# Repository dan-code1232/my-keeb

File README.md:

# my-keeb
My keeb design and documents for the hack club keeb YSWS
TOTAL OF 32 hours learning and building

This YSWS was my first hack club project. I learnt about hackclub from online and I had a great time building and completeing this project. During theis project I made a custom keyboard with programmable macro keys and learnt 3d onshape design, soldering,kicad pcb design and also about different styles layouts and mounts of keyboards.My finished project was one that i am proud of and here it is!

##AND THE FINAL RENDER::

https://cad.onshape.com/documents/12cb8831dddddaf00ecb411f/w/8d695212fe769afe4ca3f804/e/d073d4997be6d06dd7fe0af7?renderMode=0&uiState=6adc6b124070a14a067048c0

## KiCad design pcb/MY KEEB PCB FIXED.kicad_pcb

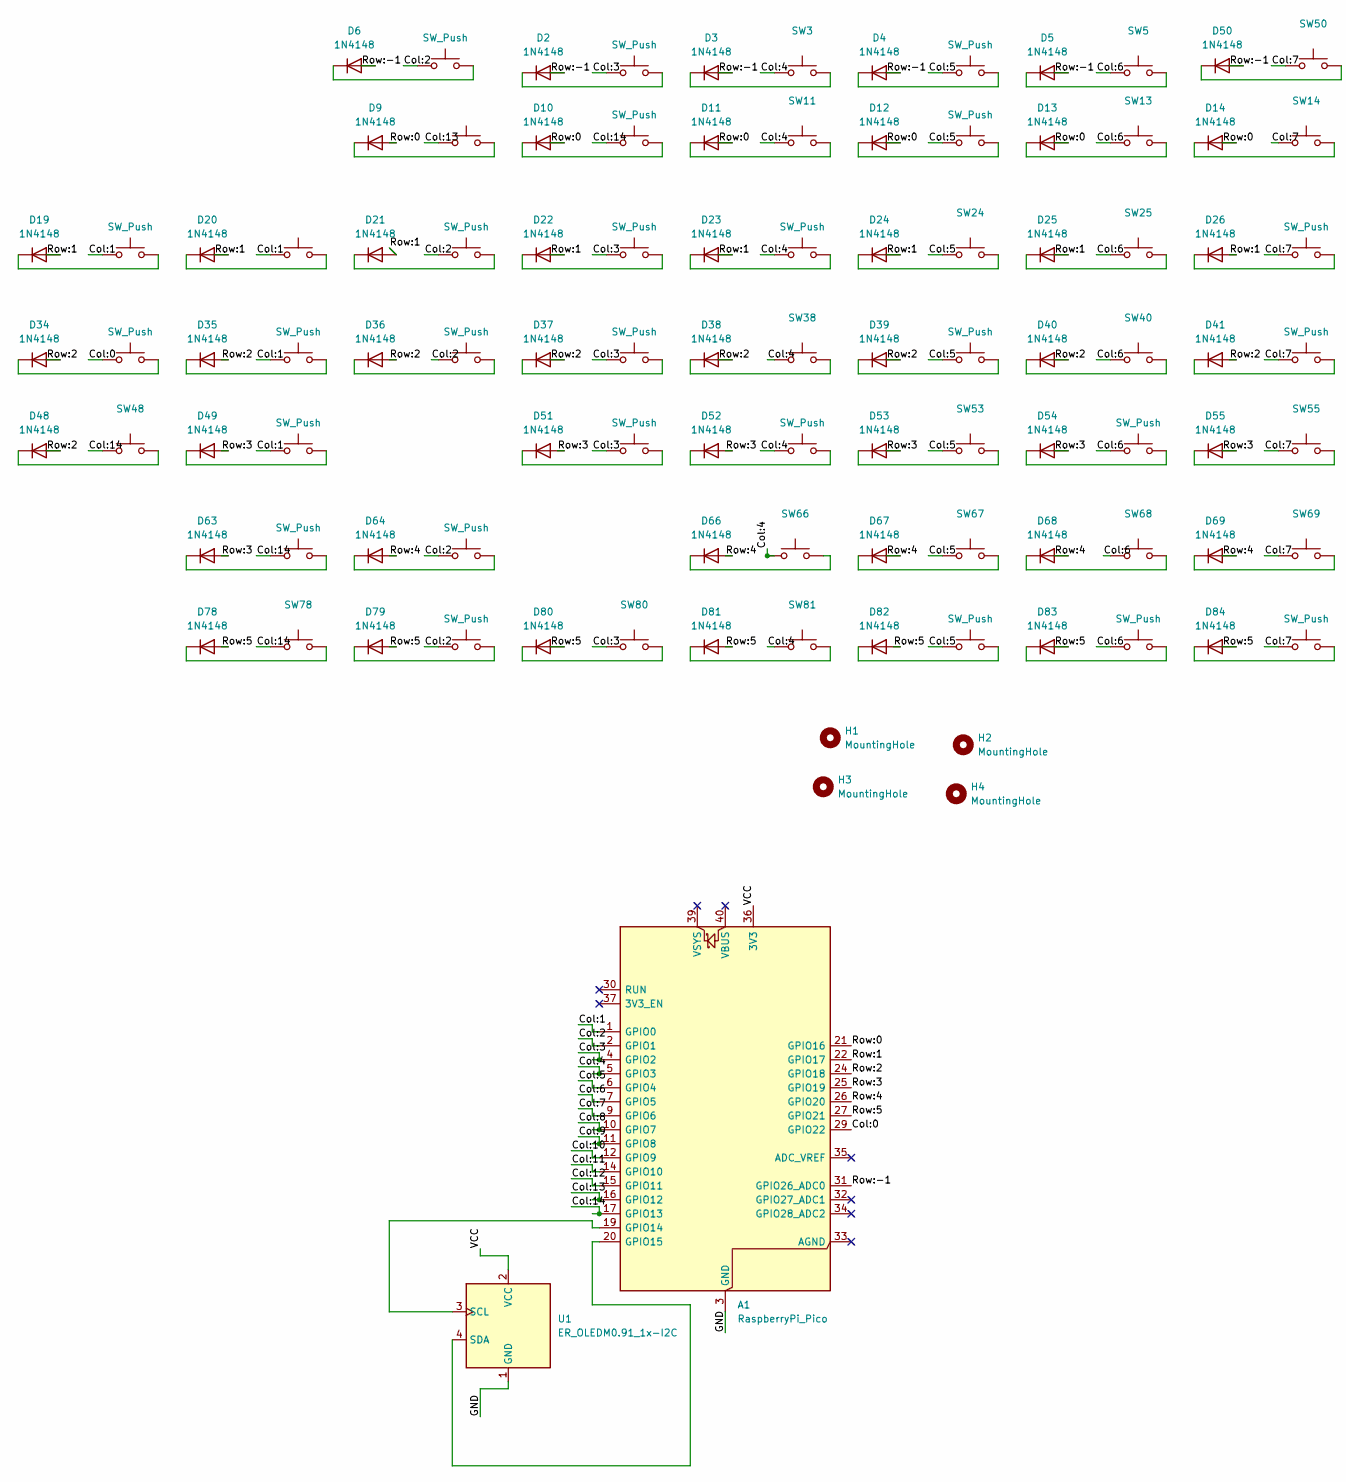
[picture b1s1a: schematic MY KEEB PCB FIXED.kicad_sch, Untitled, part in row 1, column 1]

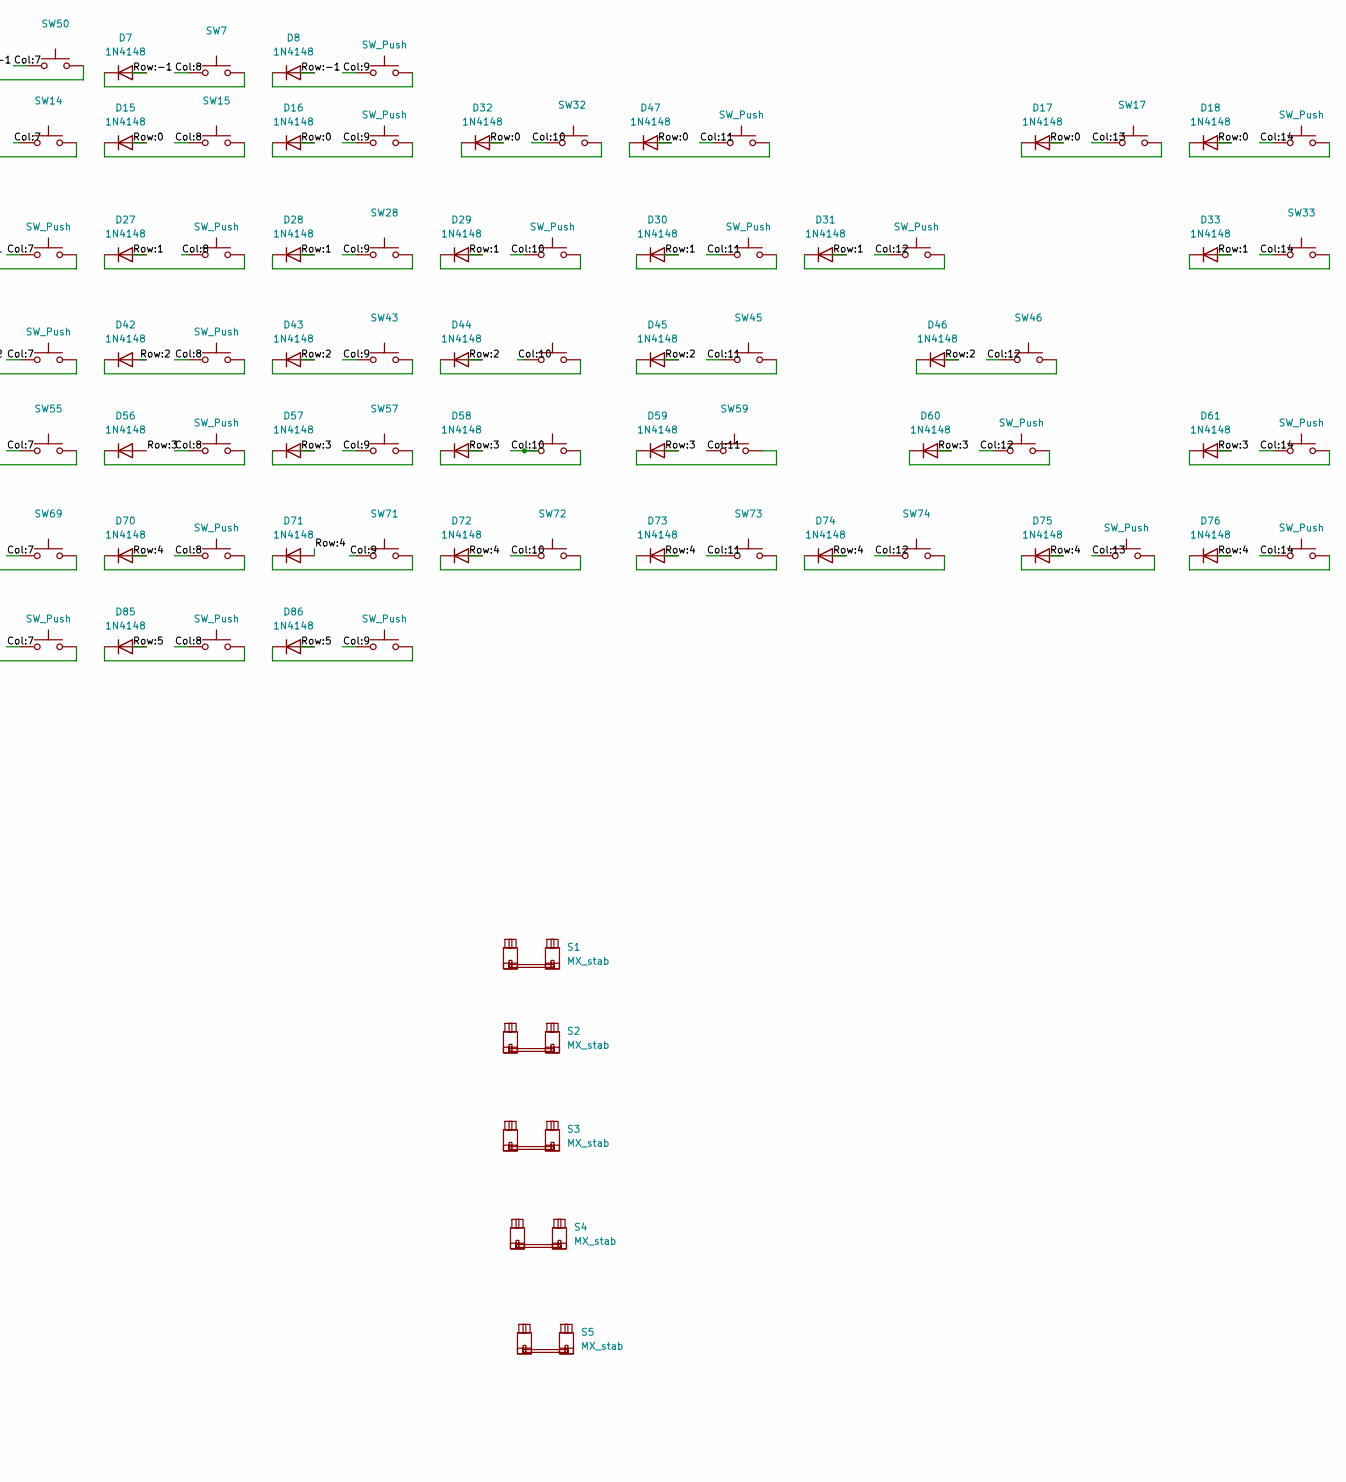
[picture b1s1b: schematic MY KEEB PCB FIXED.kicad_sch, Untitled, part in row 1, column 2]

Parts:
A1: RaspberryPi_Pico; RaspberryPi_Pico_Common_THT
D2, D3, D4, D5, D6, D7, D8, D9, D10, D11, D12, D13, D14, D15, D16, D17, D18, D19, D20, D21, D22, D23, D24, D25, D26, D27, D28, D29, D30, D31, D32, D33, D34, D35, D36, D37, D38, D39, D40, D41, D42, D43, D44, D45, D46, D47, D48, D49, D50, D51, D52, D53, D54, D55, D56, D57, D58, D59, D60, D61, D63, D64, D66, D67, D68, D69, D70, D71, D72, D73, D74, D75, D76, D78, D79, D80, D81, D82, D83, D84, D85, D86: 1N4148; D_DO-35_SOD27_P7.62mm_Horizontal
H1, H2, H3, H4: MountingHole; MountingHole_3.2mm_M3
S1, S2: MX_stab; STAB_MX_2.25u
S3: MX_stab; STAB_MX_P_6.25u
S4: MX_stab; STAB_MX_2.75u
S5: MX_stab; STAB_MX_2u
SW2, SW3, SW4, SW5, SW6, SW7, SW8, SW9, SW10, SW11, SW12, SW13, SW14, SW15, SW16, SW17, SW18, SW19, SW20, SW21, SW22, SW23, SW24, SW25, SW26, SW27, SW28, SW29, SW30, SW31, SW32, SW33, SW34, SW35, SW36, SW37, SW38, SW39, SW40, SW41, SW42, SW43, SW44, SW45, SW46, SW47, SW48, SW49, SW50, SW51, SW52, SW53, SW54, SW55, SW56, SW57, SW58, SW59, SW60, SW61, SW63, SW64, SW66, SW67, SW68, SW69, SW70, SW71, SW72, SW73, SW74, SW75, SW76, SW78, SW79, SW80, SW81, SW82, SW83, SW84, SW85, SW86: SW_Push; SW_MX_1u
U1: ER_OLEDM0.91_1x-I2C

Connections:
/Col:0: A1.29 (GPIO22), SW34.1
/Col:1: A1.1 (GPIO0), SW19.1, SW20.1, SW35.1, SW49.1
/Col:2: A1.2 (GPIO1), SW6.1, SW21.1, SW36.1, SW64.1, SW79.1
/Col:3: A1.4 (GPIO2), SW2.1, SW22.1, SW37.1, SW51.1, SW80.1
/Col:4: A1.5 (GPIO3), SW3.1, SW11.1, SW23.1, SW38.1, SW52.1, SW66.1, SW81.1
/Col:5: A1.6 (GPIO4), SW4.1, SW12.1, SW24.1, SW39.1, SW53.1, SW67.1, SW82.1
/Col:6: A1.7 (GPIO5), SW5.1, SW13.1, SW25.1, SW40.1, SW54.1, SW68.1, SW83.1
/Col:7: A1.9 (GPIO6), SW14.1, SW26.1, SW41.1, SW50.1, SW55.1, SW69.1, SW84.1
/Col:8: A1.10 (GPIO7), SW7.1, SW15.1, SW27.1, SW42.1, SW56.1, SW70.1, SW85.1
/Col:9: A1.11 (GPIO8), SW8.1, SW16.1, SW28.1, SW43.1, SW57.1, SW71.1, SW86.1
/Col:10: A1.12 (GPIO9), SW29.1, SW32.1, SW44.1, SW58.1, SW72.1
/Col:11: A1.14 (GPIO10), SW30.1, SW45.1, SW47.1, SW59.1, SW73.1
/Col:12: A1.15 (GPIO11), SW31.1, SW46.1, SW60.1, SW74.1
/Col:13: A1.16 (GPIO12), SW9.1, SW17.1, SW75.1
/Col:14: A1.17 (GPIO13), SW10.1, SW18.1, SW33.1, SW48.1, SW61.1, SW63.1, SW76.1, SW78.1
/GND: A1.3 (GND), A1.8 (GND), A1.13 (GND), A1.18 (GND), A1.23 (GND), A1.28 (GND), A1.38 (GND), U1.1 (GND)
/Row:0: A1.21 (GPIO16), D9.2 (A), D10.2 (A), D11.2 (A), D12.2 (A), D13.2 (A), D14.2 (A), D15.2 (A), D16.2 (A), D17.2 (A), D18.2 (A), D32.2 (A), D47.2 (A)
/Row:1: A1.22 (GPIO17), D19.2 (A), D20.2 (A), D21.2 (A), D22.2 (A), D23.2 (A), D24.2 (A), D25.2 (A), D26.2 (A), D27.2 (A), D28.2 (A), D29.2 (A), D30.2 (A), D31.2 (A), D33.2 (A)
/Row:2: A1.24 (GPIO18), D34.2 (A), D35.2 (A), D36.2 (A), D37.2 (A), D38.2 (A), D39.2 (A), D40.2 (A), D41.2 (A), D42.2 (A), D43.2 (A), D44.2 (A), D45.2 (A), D46.2 (A), D48.2 (A)
/Row:3: A1.25 (GPIO19), D49.2 (A), D51.2 (A), D52.2 (A), D53.2 (A), D54.2 (A), D55.2 (A), D56.2 (A), D57.2 (A), D58.2 (A), D59.2 (A), D60.2 (A), D61.2 (A), D63.2 (A)
/Row:4: A1.26 (GPIO20), D64.2 (A), D66.2 (A), D67.2 (A), D68.2 (A), D69.2 (A), D70.2 (A), D71.2 (A), D72.2 (A), D73.2 (A), D74.2 (A), D75.2 (A), D76.2 (A)
/Row:5: A1.27 (GPIO21), D78.2 (A), D79.2 (A), D80.2 (A), D81.2 (A), D82.2 (A), D83.2 (A), D84.2 (A), D85.2 (A), D86.2 (A)
/Row:-1: A1.31 (GPIO26_ADC0), D2.2 (A), D3.2 (A), D4.2 (A), D5.2 (A), D6.2 (A), D7.2 (A), D8.2 (A), D50.2 (A)
/VCC: A1.36 (3V3), U1.2 (VCC)
unnamed: A1.19 (GPIO14), U1.3 (SCL)
unnamed: A1.20 (GPIO15), U1.4 (SDA)
unnamed: D2.1 (K), SW2.2
unnamed: D3.1 (K), SW3.2
unnamed: D4.1 (K), SW4.2
unnamed: D5.1 (K), SW5.2
unnamed: D6.1 (K), SW6.2
unnamed: D7.1 (K), SW7.2
unnamed: D8.1 (K), SW8.2
unnamed: D9.1 (K), SW9.2
unnamed: D10.1 (K), SW10.2
unnamed: D11.1 (K), SW11.2
unnamed: D12.1 (K), SW12.2
unnamed: D13.1 (K), SW13.2
unnamed: D14.1 (K), SW14.2
unnamed: D15.1 (K), SW15.2
unnamed: D16.1 (K), SW16.2
unnamed: D17.1 (K), SW17.2
unnamed: D18.1 (K), SW18.2
unnamed: D19.1 (K), SW19.2
unnamed: D20.1 (K), SW20.2
unnamed: D21.1 (K), SW21.2
unnamed: D22.1 (K), SW22.2
unnamed: D23.1 (K), SW23.2
unnamed: D24.1 (K), SW24.2
unnamed: D25.1 (K), SW25.2
unnamed: D26.1 (K), SW26.2
unnamed: D27.1 (K), SW27.2
unnamed: D28.1 (K), SW28.2
unnamed: D29.1 (K), SW29.2
unnamed: D30.1 (K), SW30.2
unnamed: D31.1 (K), SW31.2
unnamed: D32.1 (K), SW32.2
unnamed: D33.1 (K), SW33.2
unnamed: D34.1 (K), SW34.2
unnamed: D35.1 (K), SW35.2
unnamed: D36.1 (K), SW36.2
unnamed: D37.1 (K), SW37.2
unnamed: D38.1 (K), SW38.2
unnamed: D39.1 (K), SW39.2
unnamed: D40.1 (K), SW40.2
unnamed: D41.1 (K), SW41.2
unnamed: D42.1 (K), SW42.2
unnamed: D43.1 (K), SW43.2
unnamed: D44.1 (K), SW44.2
unnamed: D45.1 (K), SW45.2
unnamed: D46.1 (K), SW46.2
unnamed: D47.1 (K), SW47.2
unnamed: D48.1 (K), SW48.2
unnamed: D49.1 (K), SW49.2
unnamed: D50.1 (K), SW50.2
unnamed: D51.1 (K), SW51.2
unnamed: D52.1 (K), SW52.2
unnamed: D53.1 (K), SW53.2
unnamed: D54.1 (K), SW54.2
unnamed: D55.1 (K), SW55.2
unnamed: D56.1 (K), SW56.2
unnamed: D57.1 (K), SW57.2
unnamed: D58.1 (K), SW58.2
unnamed: D59.1 (K), SW59.2
unnamed: D60.1 (K), SW60.2
unnamed: D61.1 (K), SW61.2
unnamed: D63.1 (K), SW63.2
unnamed: D64.1 (K), SW64.2
unnamed: D66.1 (K), SW66.2
unnamed: D67.1 (K), SW67.2
unnamed: D68.1 (K), SW68.2
unnamed: D69.1 (K), SW69.2
unnamed: D70.1 (K), SW70.2
unnamed: D71.1 (K), SW71.2
unnamed: D72.1 (K), SW72.2
unnamed: D73.1 (K), SW73.2
unnamed: D74.1 (K), SW74.2
unnamed: D75.1 (K), SW75.2
unnamed: D76.1 (K), SW76.2
unnamed: D78.1 (K), SW78.2
unnamed: D79.1 (K), SW79.2
unnamed: D80.1 (K), SW80.2
unnamed: D81.1 (K), SW81.2
unnamed: D82.1 (K), SW82.2
unnamed: D83.1 (K), SW83.2
unnamed: D84.1 (K), SW84.2
unnamed: D85.1 (K), SW85.2
unnamed: D86.1 (K), SW86.2

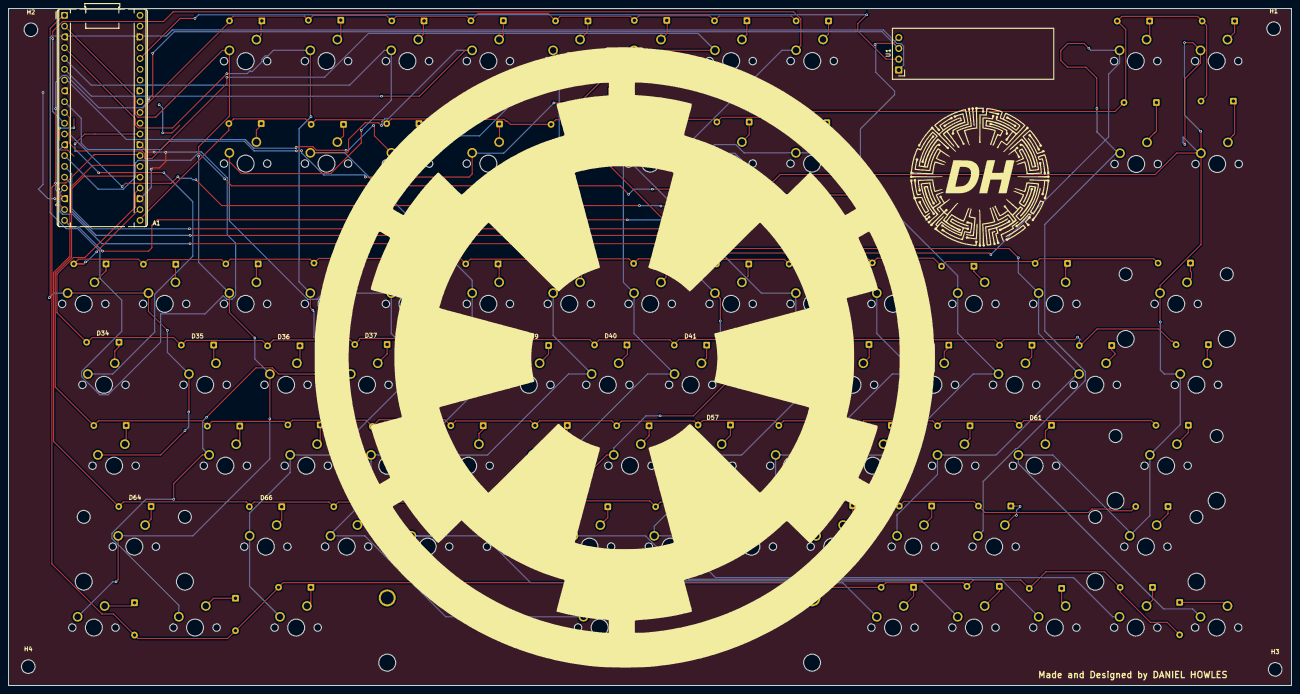
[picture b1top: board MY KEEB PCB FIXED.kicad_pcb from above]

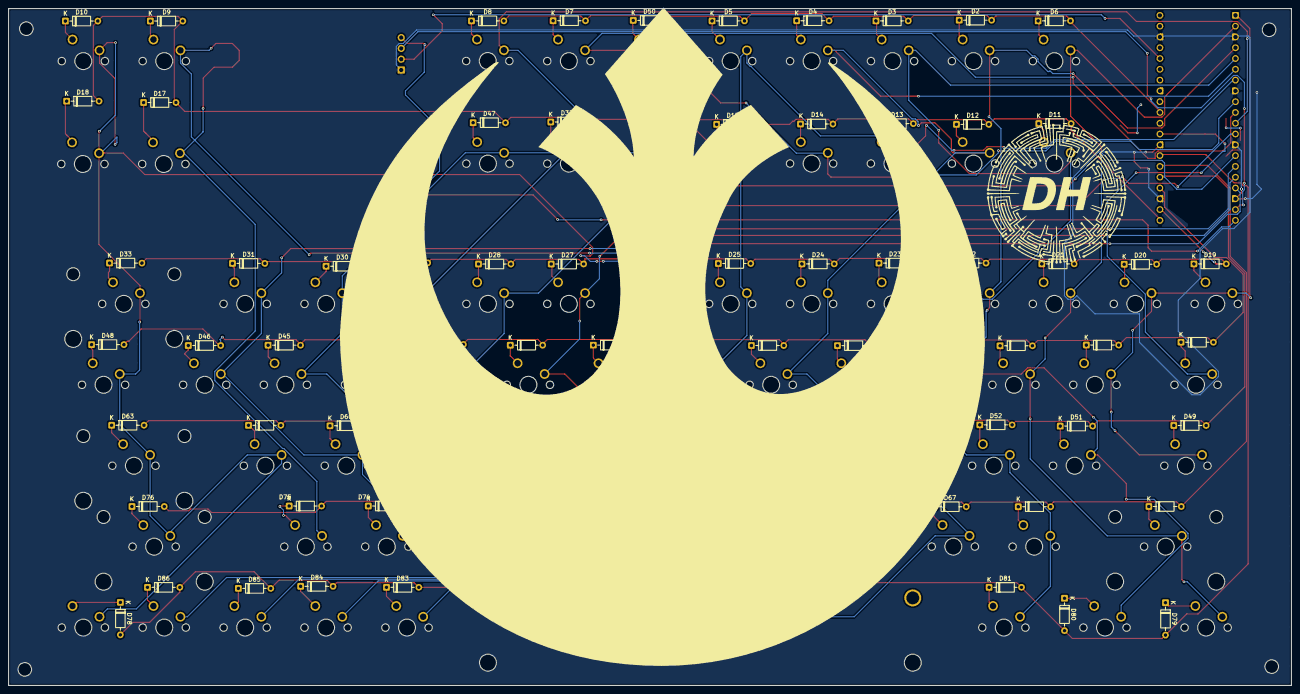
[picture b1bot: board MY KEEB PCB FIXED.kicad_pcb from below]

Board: 2 copper layers, 302.0 x 159.3 mm, 175 parts (82 on the bottom side), 107 nets.

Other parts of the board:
SW50#2: SW_Push; SW_MX_1u
